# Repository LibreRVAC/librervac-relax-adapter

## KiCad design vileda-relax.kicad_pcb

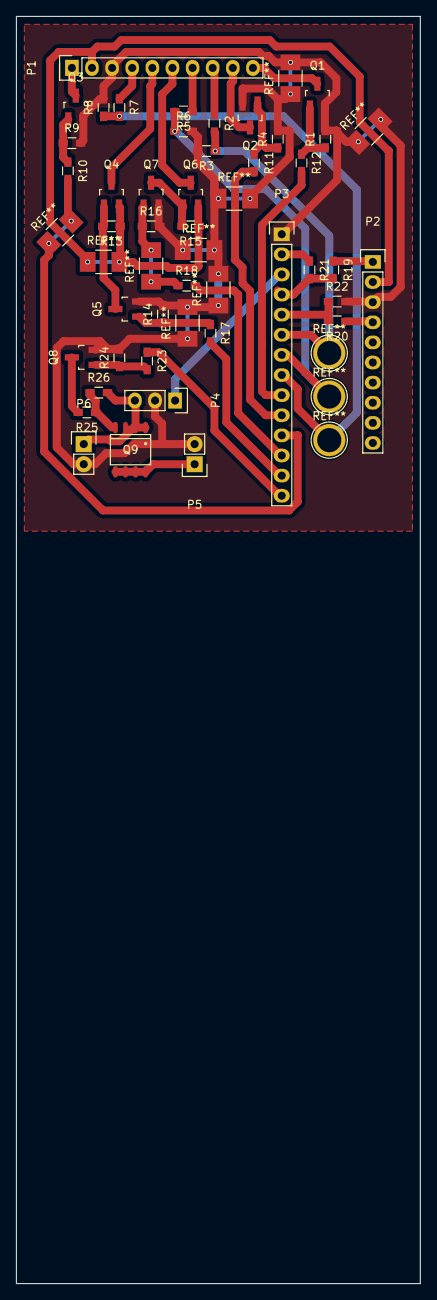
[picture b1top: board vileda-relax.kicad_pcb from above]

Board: 2 copper layers, 51.0 x 160.0 mm, 41 parts (0 on the bottom side), 37 nets.

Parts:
P1: Button Board; Pin_Header_Straight_1x10
P2: Main Board; Pin_Header_Straight_1x10
P3: Linux Board; Pin_Header_Straight_1x14
P4: DC/DC; Pin_Header_Straight_1x03
P5: Main Board Power; Pin_Header_Straight_1x02
P6: Battery; Pin_Header_Straight_1x02
Q1, Q2, Q3, Q5, Q7, Q8: Q_NMOS_GSD; SOT-23_Handsoldering
Q4, Q6: Q_PMOS_GSD; SOT-23_Handsoldering
Q9: Q_PMOS_GSD; SO-8
R1, R2, R3, R4, R5, R6, R7, R8, R9, R10, R11, R12, R13, R14, R15, R16, R17, R18, R19, R20, R21, R22, R23, R24, R25, R26: R; R_0603_HandSoldering

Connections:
+5VP: P1.2, P2.2, Q4.2, Q6.2, R13.1, R15.1
/+: P4.3, P6.1, Q9.1, Q9.2, Q9.3, R26.2
/BTN1: P1.4, R7.1
/BTN2: P1.7, R5.1
/BTN3: P1.8, R2.1
/RxD: P2.1, R19.1
/TxD: P2.4, R20.1
unnamed: P1.1, Q3.3
unnamed: P1.5, Q4.3
unnamed: P1.6, Q6.3
unnamed: P1.9, Q2.3
unnamed: P1.10, Q1.3
unnamed: P5.1, Q9.5, Q9.6, Q9.7, Q9.8
unnamed: Q1.1, R1.1, R12.1
unnamed: Q2.1, R4.1, R11.1
unnamed: Q3.1, R9.1, R10.1
unnamed: Q4.1, Q5.3, R13.2
unnamed: Q5.1, R14.1, R17.1
unnamed: Q6.1, Q7.3, R15.2
unnamed: Q7.1, R16.1, R18.1
unnamed: Q8.1, R23.2, R24.1
unnamed: Q8.3, R25.2
unnamed: Q9.4, R25.1, R26.1
RP_3V3_1: P3.2, R21.1
RP_5V_4: P3.3, P4.1
RP_BUTTON1_7: P3.6, R2.2, R3.1
RP_BUTTON2_11: P3.7, R5.2, R6.1
RP_BUTTON3_13: P3.8, R7.2, R8.1
RP_GND_6: P1.3, P2.3, P3.1, P4.2, P5.2, P6.2, Q1.2, Q2.2, Q3.2, Q5.2, Q7.2, Q8.2, R1.2, R3.2, R4.2, R6.2, R8.2, R9.2, R14.2, R16.2, R22.2, R24.2
RP_LED1_15: P3.9, R12.2
RP_LED2_16: P3.10, R11.2
RP_LED3_18: P3.11, R10.2
RP_LED?_31: P3.12, R18.2
RP_LED_OK_29: P3.13, R17.2
RP_POWERUP_MAIN_BOARD_22: P3.14, R23.1
RP_RxD_10: P3.5, R20.2, R22.1
RP_TxD_8: P3.4, R19.2, R21.2

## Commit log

2016-05-15 Published
